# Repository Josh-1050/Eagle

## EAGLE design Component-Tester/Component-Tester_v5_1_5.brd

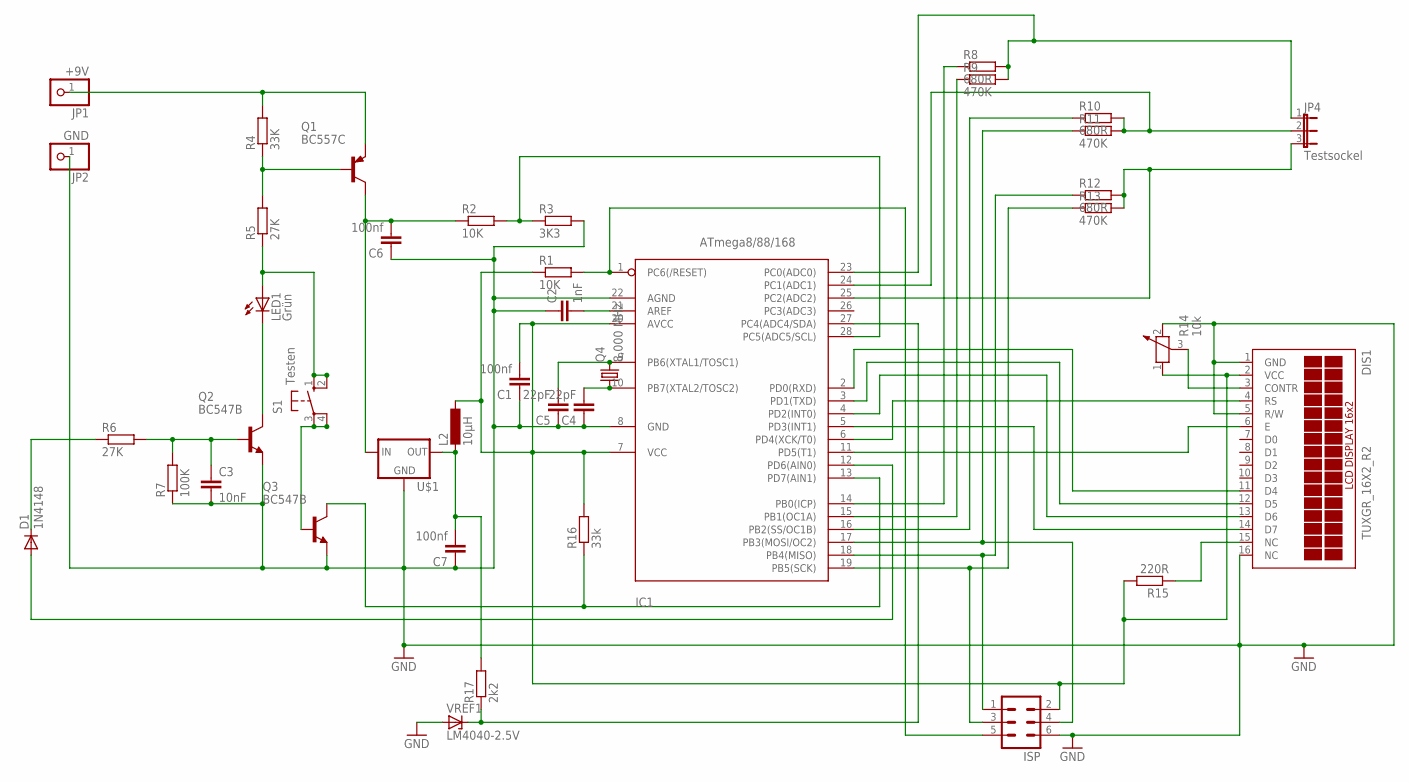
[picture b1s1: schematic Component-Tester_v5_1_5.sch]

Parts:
C1, C6, C7: 100nf; C5B3.5
C2: 1nF; C2.5-2
C3: 10nF; C5B3.5
C4, C5: 22pF; C025-025X050
D1: 1N4148; DO35-7
DIS1: TUXGR_16X2_R2
IC1: ATmega8/88/168; DIL28-3
ISP: ML6L
JP1: +9V; 1X01
JP2: GND; 1X01
JP4: Testsockel; JP2
L2: 10µH; 0207/10
LED1: Grün; LED5MM
Q1: BC557C; TO92-EBC
Q2, Q3: BC547B; TO92
Q4: 8,000 MHz; HC49/S
R1, R2: 10K; 0207/10
R3: 3K3; 0207/10
R4: 33K; 0207/10
R5, R6: 27K; 0207/10
R7: 100K; 0207/10
R8, R10, R12: 680R; 0207/10
R9, R11, R13: 470K; 0207/10
R14: 10k; PT-10
R15: 220R; 0207/10
R16: 33k; 0207/10
R17: 2k2; 0207/10
S1: Testen; B3F-10XX
U$1: MCP1702-5002; TO92-LOWDROP
VREF1: LM4040-2.5V; TO92-VREF

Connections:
GND: C1.1, C2.1, C3.2, C4.1, C5.1, C6.1, C7.1, DIS1.1 (GND), DIS1.5 (R/W), DIS1.16 (NC), IC1.8 (GND), IC1.22 (AGND), ISP.6, JP2.1, Q2.1 (E), Q3.1 (E), R3.2, R7.1, R14.2, U$1.GND, VREF1.-
unnamed: C6.2, Q1.C, R2.1, U$1.IN
unnamed: IC1.1 (PC6(/RESET)), ISP.5, R1.2
unnamed: C2.2, IC1.21 (AREF)
unnamed: Q1.B, R4.1, R5.2
unnamed: IC1.28 (PC5(ADC5/SCL)), R2.2, R3.1
unnamed: C1.2, DIS1.2 (VCC), IC1.7 (VCC), IC1.20 (AVCC), ISP.2, L2.1, R1.1, R14.1, R15.2, R16.2
unnamed: LED1.K (C), Q2.3 (C)
unnamed: IC1.13 (PD7(AIN1)), Q3.3 (C), R16.1
unnamed: C3.1, Q2.2 (B), R6.2, R7.2
unnamed: D1.A, IC1.12 (PD6(AIN0))
unnamed: IC1.25 (PC2(ADC2)), JP4.3, R12.2, R13.2
unnamed: Q3.2 (B), S1.3, S1.4 (P1)
unnamed: IC1.24 (PC1(ADC1)), JP4.2, R10.2, R11.2
unnamed: IC1.23 (PC0(ADC0)), JP4.1, R8.2, R9.2
unnamed: C7.2, L2.2, R17.2, U$1.OUT
unnamed: IC1.18 (PB4(MISO)), ISP.1, R12.1
unnamed: IC1.14 (PB0(ICP)), R8.1
unnamed: IC1.15 (PB1(OC1A)), R9.1
unnamed: IC1.16 (PB2(SS/OC1B)), R10.1
unnamed: IC1.19 (PB5(SCK)), ISP.3, R13.1
unnamed: LED1.A, R5.1, S1.1 (S), S1.2 (S1)
unnamed: DIS1.3 (CONTR), R14.3
unnamed: DIS1.4 (RS), IC1.6 (PD4(XCK/T0))
unnamed: DIS1.6 (E), IC1.11 (PD5(T1))
unnamed: DIS1.11 (D4), IC1.2 (PD0(RXD))
unnamed: DIS1.12 (D5), IC1.3 (PD1(TXD))
unnamed: DIS1.13 (D6), IC1.4 (PD2(INT0))
unnamed: DIS1.14 (D7), IC1.5 (PD3(INT1))
unnamed: C4.2, IC1.10 (PB7(XTAL2/TOSC2)), Q4.1
unnamed: DIS1.15 (NC), R15.1
unnamed: JP1.1, Q1.E, R4.2
unnamed: C5.2, IC1.9 (PB6(XTAL1/TOSC1)), Q4.2
unnamed: D1.C, R6.1
unnamed: IC1.17 (PB3(MOSI/OC2)), ISP.4, R11.1
unnamed: IC1.27 (PC4(ADC4/SDA)), R17.1, VREF1.+

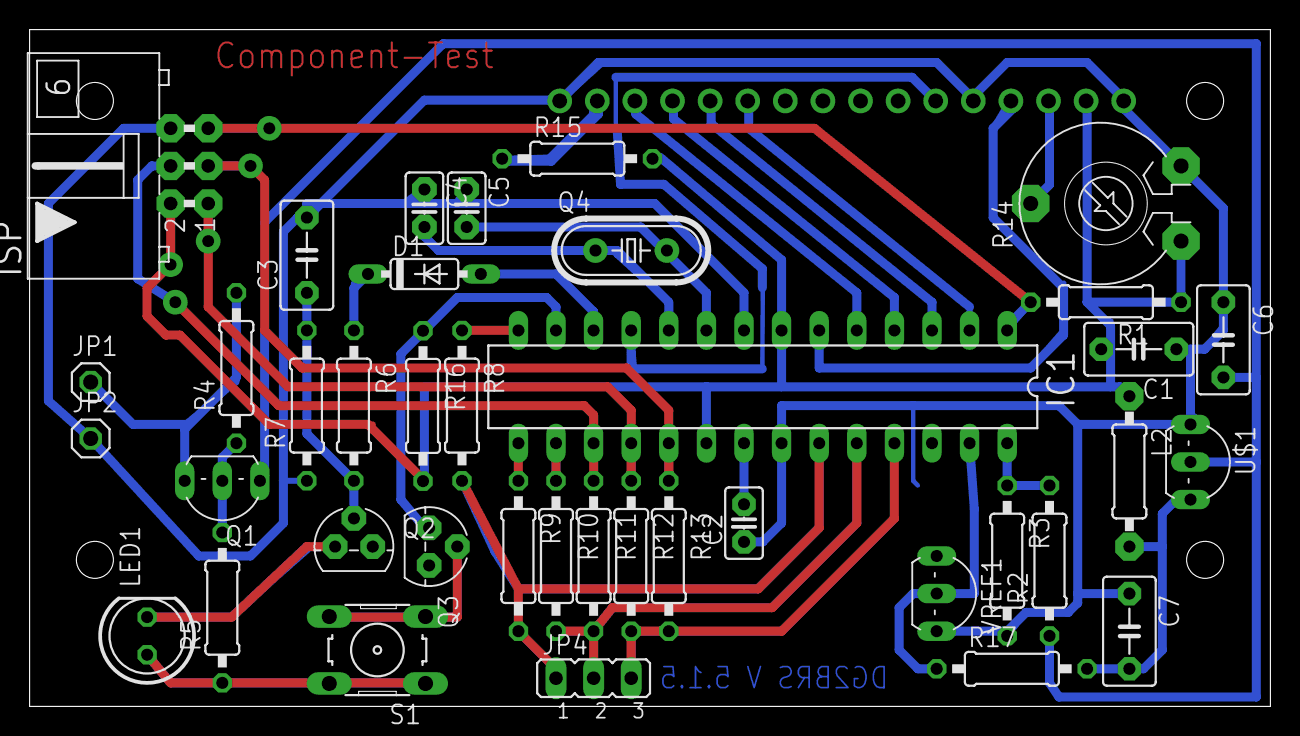
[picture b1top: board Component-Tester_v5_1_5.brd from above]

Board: 2 copper layers, 83.8 x 45.7 mm, 40 parts (1 on the bottom side), 36 nets.

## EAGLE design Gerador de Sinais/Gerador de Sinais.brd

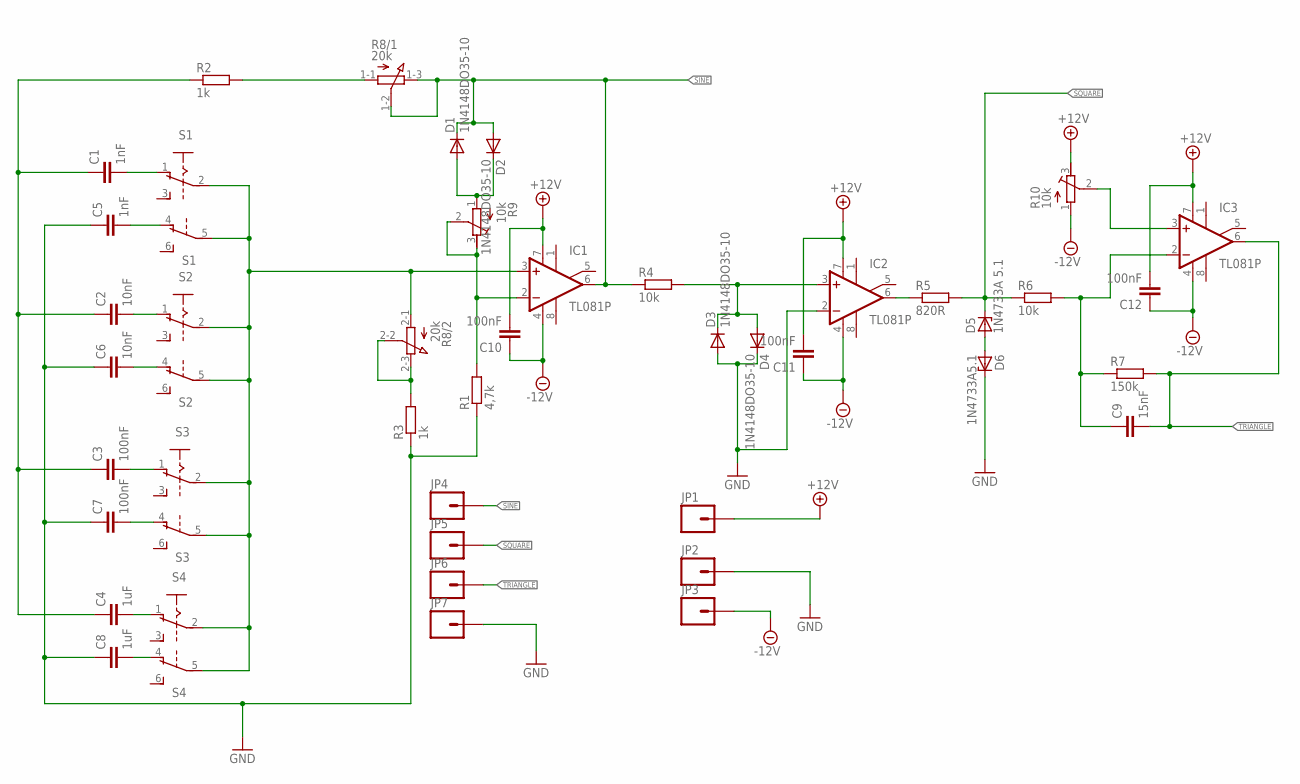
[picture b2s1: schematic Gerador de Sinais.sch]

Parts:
C1, C5: 1nF; C050-050X075
C2, C6: 10nF; C050-050X075
C3, C7, C10, C11, C12: 100nF; C050-050X075
C4, C8: 1uF; C050-050X075
C9: 15nF; C050-050X075
D1, D2, D3, D4: 1N4148DO35-10; DO35-10
D5: 1N4733A 5.1; ZDIO-10
D6: 1N4733A5.1; ZDIO-10
IC1, IC2, IC3: TL081P; DIL08
JP1, JP2, JP3, JP4, JP5, JP6, JP7: M01OFFSET; 1X01_OFFSET
R1: 4,7k; 0207/10
R2, R3: 1k; 0207/10
R4, R6: 10k; 0207/10
R5: 820R; 0207/10
R7: 150k; 0207/10
R8: 20k; 3RP/1610G
R9, R10: 10k; RTRIM3296X
S1, S2, S3, S4: A68-A31

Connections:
+12V: C10.2, C11.2, C12.2, IC1.7 (V+), IC2.7 (V+), IC3.7 (V+), JP1.1, R10.3 (E)
-12V: C10.1, C11.1, C12.1, IC1.4 (V-), IC2.4 (V-), IC3.4 (V-), JP3.1, R10.1 (A)
GND: C5.1, C6.1, C7.1, C8.1, D3.A, D4.C, D6.C, IC2.2 (-IN), JP2.1, JP7.1, R1.1, R3.1
unnamed: IC1.2 (-IN), R1.2, R9.2 (S), R9.3 (E)
unnamed: D5.A, D6.A
unnamed: R3.2, R8.2-2 (S), R8.2-3 (E)
unnamed: R2.2, R8.1-1 (A)
unnamed: IC1.3 (+IN), R8.2-1 (A), S1.2, S1.5, S2.2, S2.5, S3.2, S3.5, S4.2, S4.5
unnamed: D1.A, D2.C, R9.1 (A)
unnamed: C1.2, S1.1 (O)
unnamed: C5.2, S1.4 (O)
unnamed: C2.2, S2.1 (O)
unnamed: C6.2, S2.4 (O)
unnamed: C3.2, S3.1 (O)
unnamed: C4.2, S4.1 (O)
unnamed: C7.2, S3.4 (O)
unnamed: C8.2, S4.4 (O)
unnamed: C1.1, C2.1, C3.1, C4.1, R2.1
unnamed: IC2.6 (OUT), R5.1
unnamed: D3.C, D4.A, IC2.3 (+IN), R4.2
unnamed: C9.1, IC3.2 (-IN), R6.2, R7.1
unnamed: IC3.3 (+IN), R10.2 (S)
SINE: D1.C, D2.A, IC1.6 (OUT), JP4.1, R4.1, R8.1-2 (S), R8.1-3 (E)
SQUARE: D5.C, JP5.1, R5.2, R6.1
TRIANGLE: C9.2, IC3.6 (OUT), JP6.1, R7.2

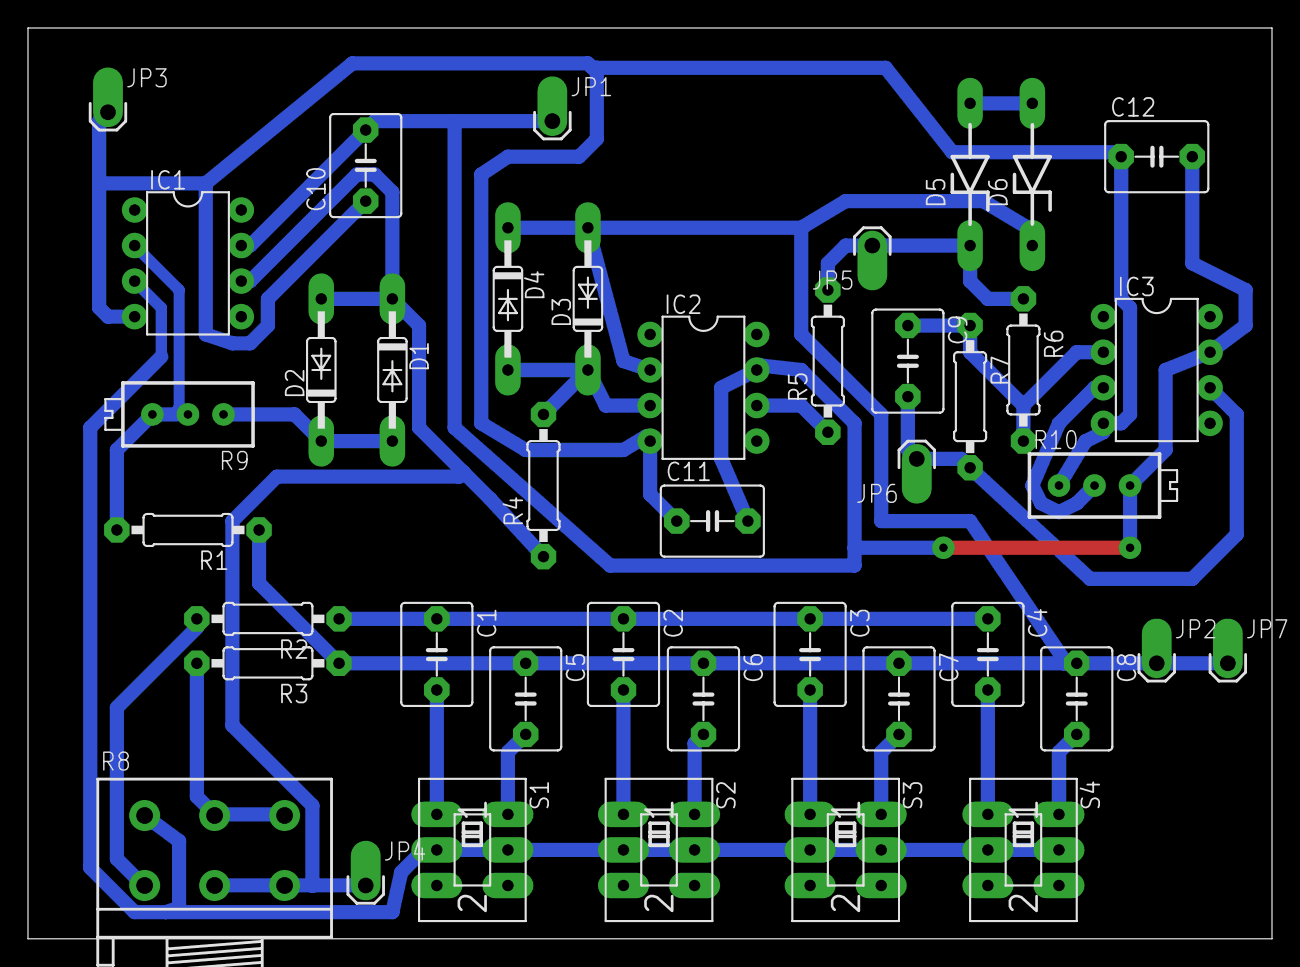
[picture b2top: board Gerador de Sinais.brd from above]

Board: 2 copper layers, 88.9 x 65.1 mm, 42 parts (0 on the bottom side), 25 nets.

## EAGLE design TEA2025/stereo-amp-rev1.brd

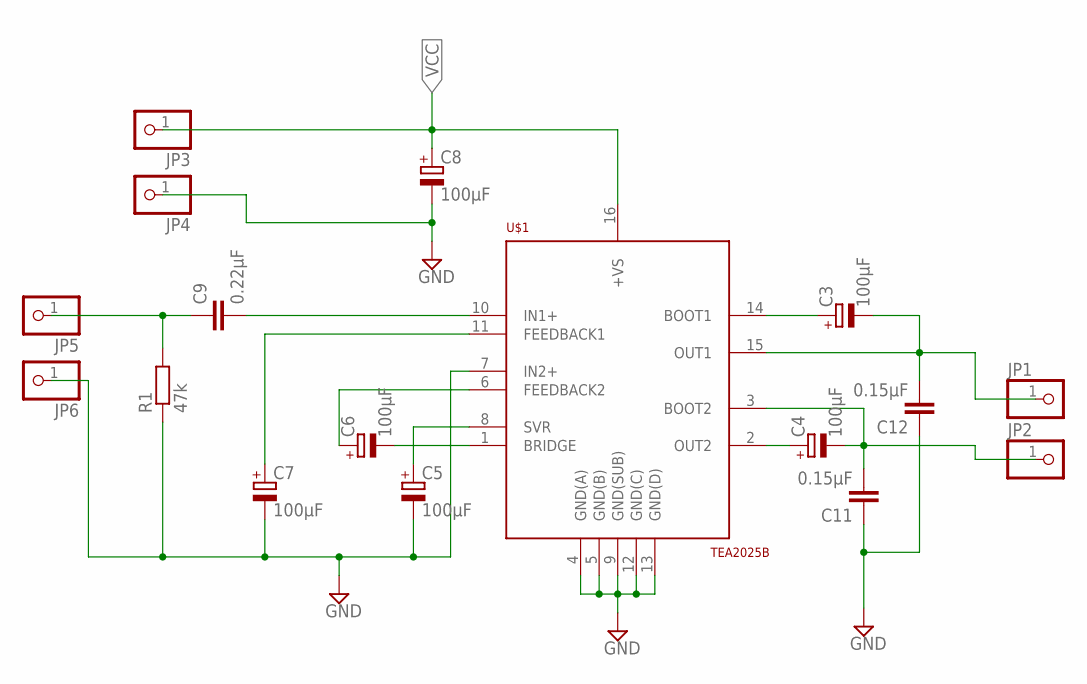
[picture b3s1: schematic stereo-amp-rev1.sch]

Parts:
C3, C4, C5, C6, C7, C8: 100µF; E2,5-7
C9: 0.22µF; C050-024X044
C11, C12: 0.15µF; C050-024X044
JP1, JP2, JP3, JP4, JP5, JP6: PINHD-1X1; 1X01
R1: 47k; 0207/10
U$1: TEA2025B; DIL16

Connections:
GND: C5.-, C7.-, C8.-, C11.1, C12.1, JP4.1, JP6.1, R1.1, U$1.4 (GND(A)), U$1.5 (GND(B)), U$1.7 (IN2+), U$1.9 (GND(SUB)), U$1.12 (GND(C)), U$1.13 (GND(D))
unnamed: C9.2, U$1.10 (IN1+)
unnamed: C6.-, U$1.1 (BRIDGE)
unnamed: C7.+, U$1.11 (FEEDBACK1)
unnamed: C6.+, U$1.6 (FEEDBACK2)
unnamed: C5.+, U$1.8 (SVR)
unnamed: C4.+, U$1.2 (OUT2)
unnamed: C4.-, C11.2, JP2.1, U$1.3 (BOOT2)
unnamed: C3.+, U$1.14 (BOOT1)
unnamed: C3.-, C12.2, JP1.1, U$1.15 (OUT1)
unnamed: C9.1, JP5.1, R1.2
VCC: C8.+, JP3.1, U$1.16 (+VS)

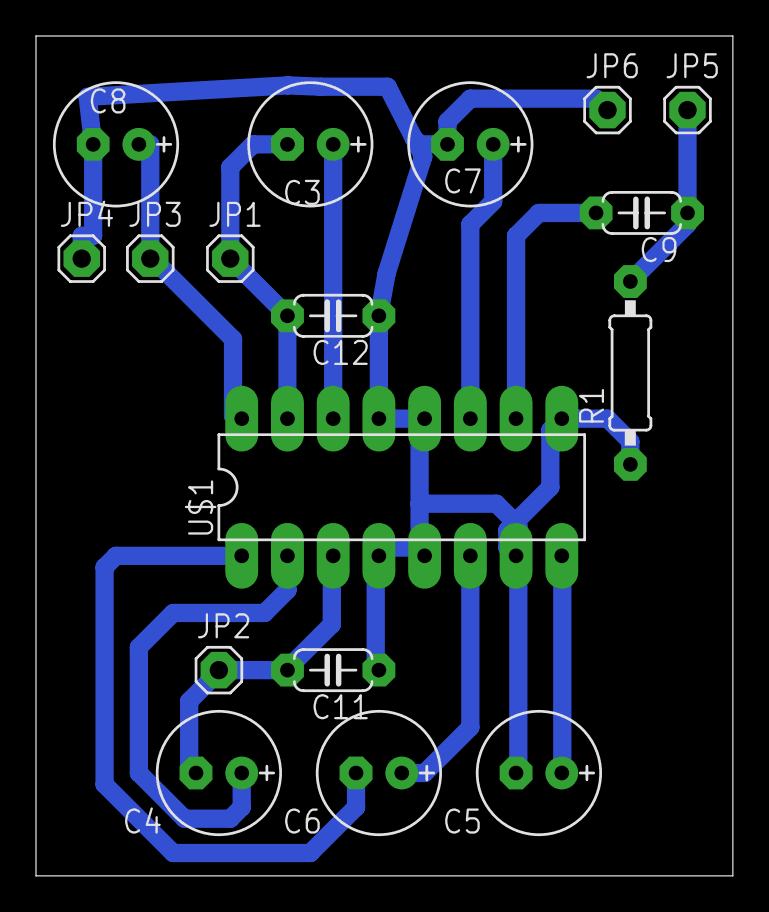
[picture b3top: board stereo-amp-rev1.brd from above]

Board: 2 copper layers, 38.7 x 46.7 mm, 17 parts (0 on the bottom side), 12 nets.

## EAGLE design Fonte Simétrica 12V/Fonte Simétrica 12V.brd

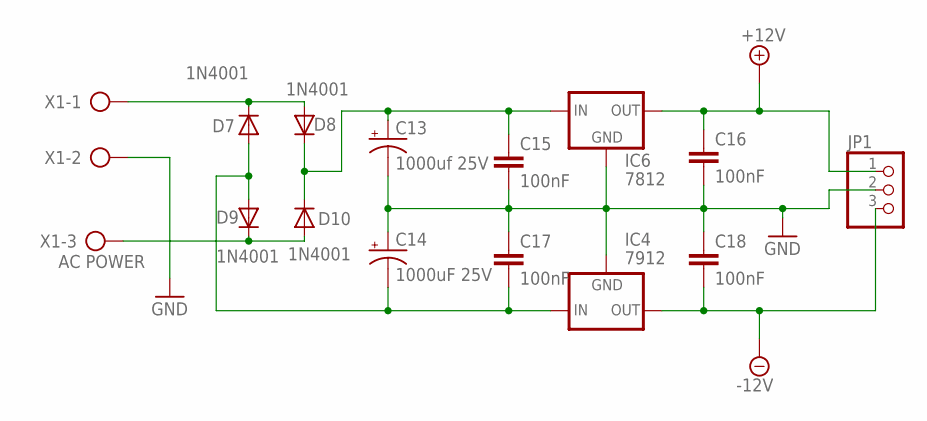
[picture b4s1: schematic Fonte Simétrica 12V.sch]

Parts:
C13: 1000uf 25V; E5-10,5
C14: 1000uF 25V; E5-10,5
C15, C16, C17, C18: 100nF; C025-040X050
D7, D8, D9, D10: 1N4001; DO41-10
IC4: 7912; 79XXS
IC6: 7812; 78XXS
JP1: PINHD-1X3; 1X03
X1: AC POWER; AK500/3

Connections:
+12V: C16.1, IC6.OUT, JP1.1
-12V: C18.2, IC4.OUT, JP1.3
GND: C13.-, C14.+, C15.2, C16.2, C17.1, C18.1, IC4.GND, IC6.GND, JP1.2, X1.2
unnamed: C14.-, C17.2, D7.A, D9.A, IC4.IN
unnamed: C13.+, C15.1, D8.C, D10.C, IC6.IN
unnamed: D7.C, D8.A, X1.1
unnamed: D9.C, D10.A, X1.3

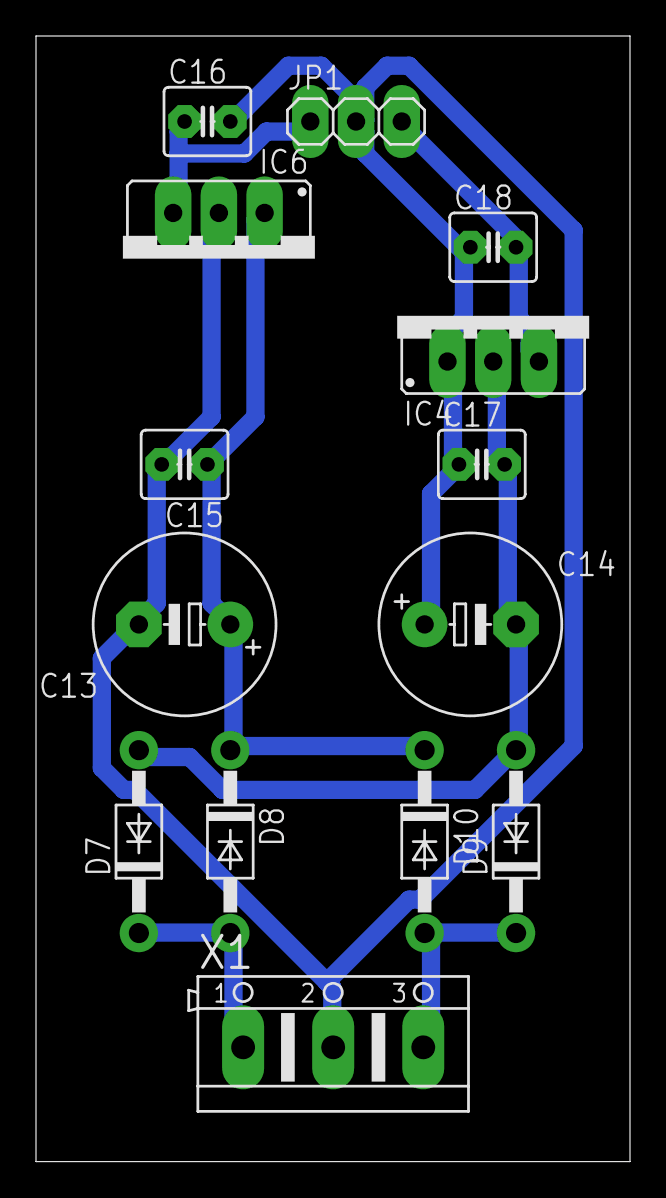
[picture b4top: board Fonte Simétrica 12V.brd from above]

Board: 2 copper layers, 33.0 x 62.5 mm, 14 parts (0 on the bottom side), 7 nets.

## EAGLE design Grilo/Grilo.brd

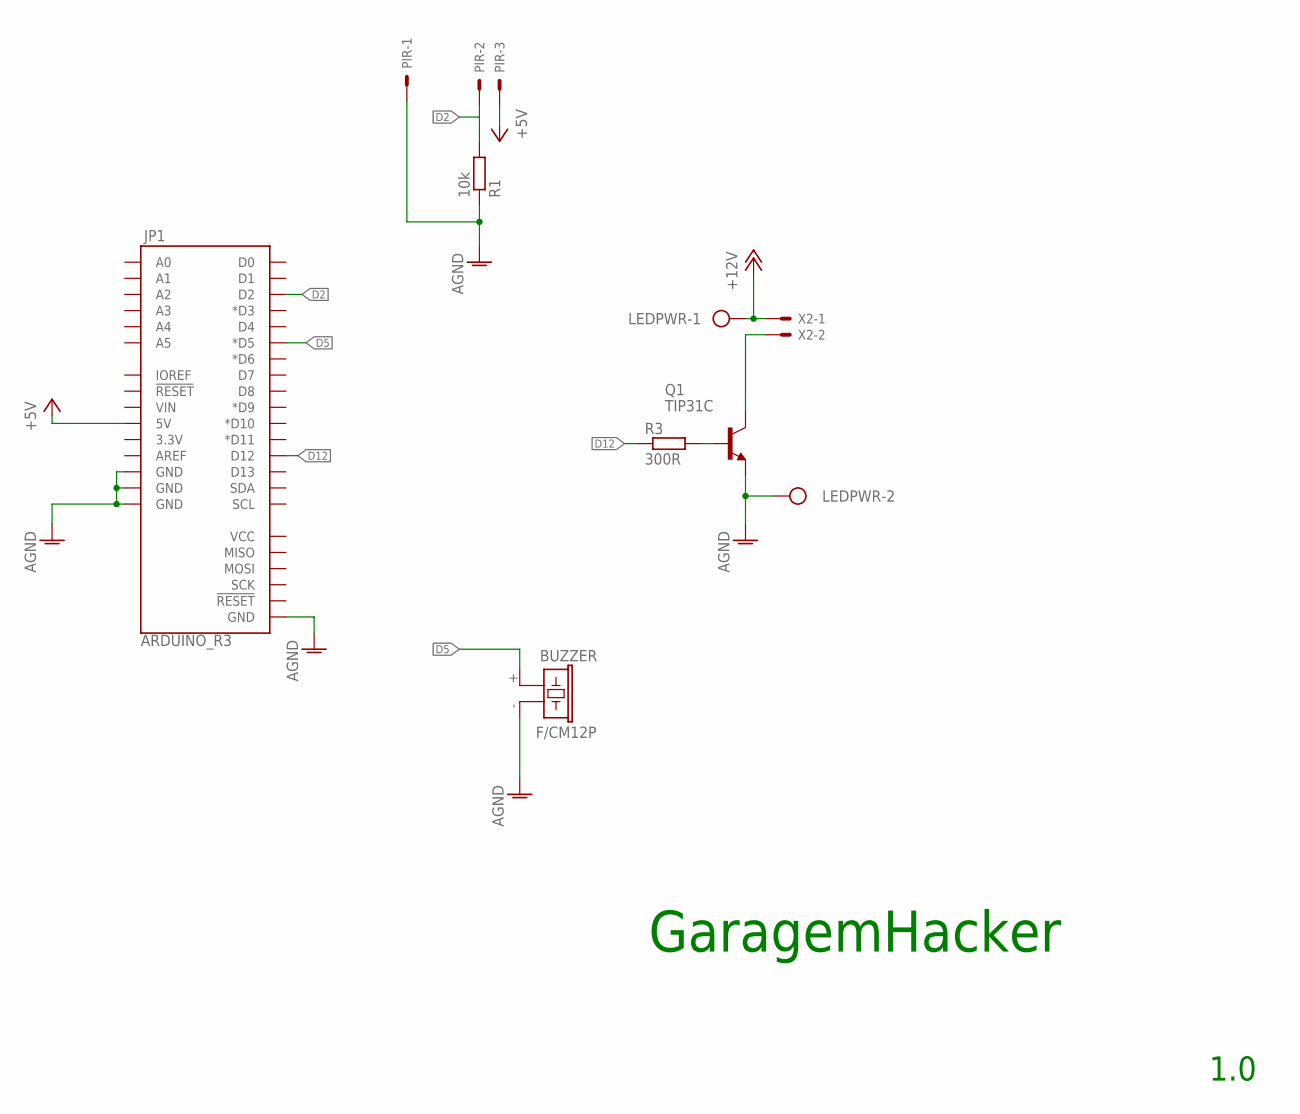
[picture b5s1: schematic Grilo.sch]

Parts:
BUZZER: F/CM12P
JP1: ARDUINO_R3
LEDPWR: AK500/2
PIR: KK-156-3
Q1: TIP31C; TO220V
R1: 10k; 0207/10
R3: 300R; 0207/10
X2: KK-156-2

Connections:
+5V: JP1.5V, PIR.3
+12V: LEDPWR.1, X2.1
AGND: BUZZER.- (2), JP1.GND@1 (GND), JP1.GND@2 (GND), JP1.GND@3 (GND), JP1.GND@4 (GND), LEDPWR.2, PIR.1, Q1.3 (E), R1.1
D2: JP1.D2, PIR.2, R1.2
D5: BUZZER.+ (1), JP1.D5 (*D5)
D12: JP1.D12, R3.1
unnamed: Q1.1 (B), R3.2
unnamed: Q1.2 (C), X2.2

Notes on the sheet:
1.0
GaragemHacker

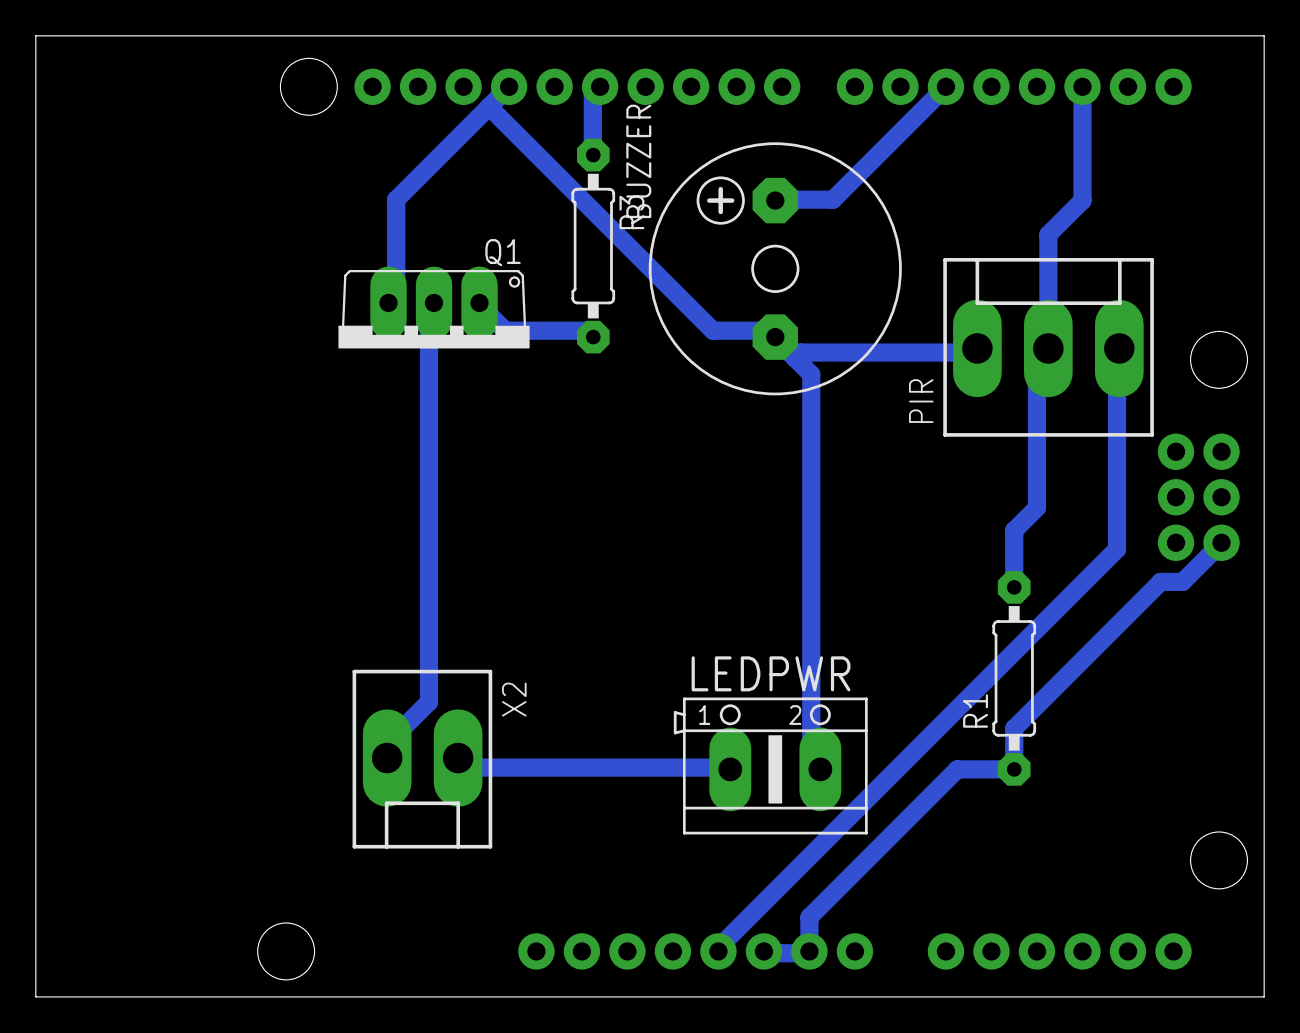
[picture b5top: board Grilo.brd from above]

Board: 2 copper layers, 68.6 x 53.6 mm, 8 parts (0 on the bottom side), 8 nets.

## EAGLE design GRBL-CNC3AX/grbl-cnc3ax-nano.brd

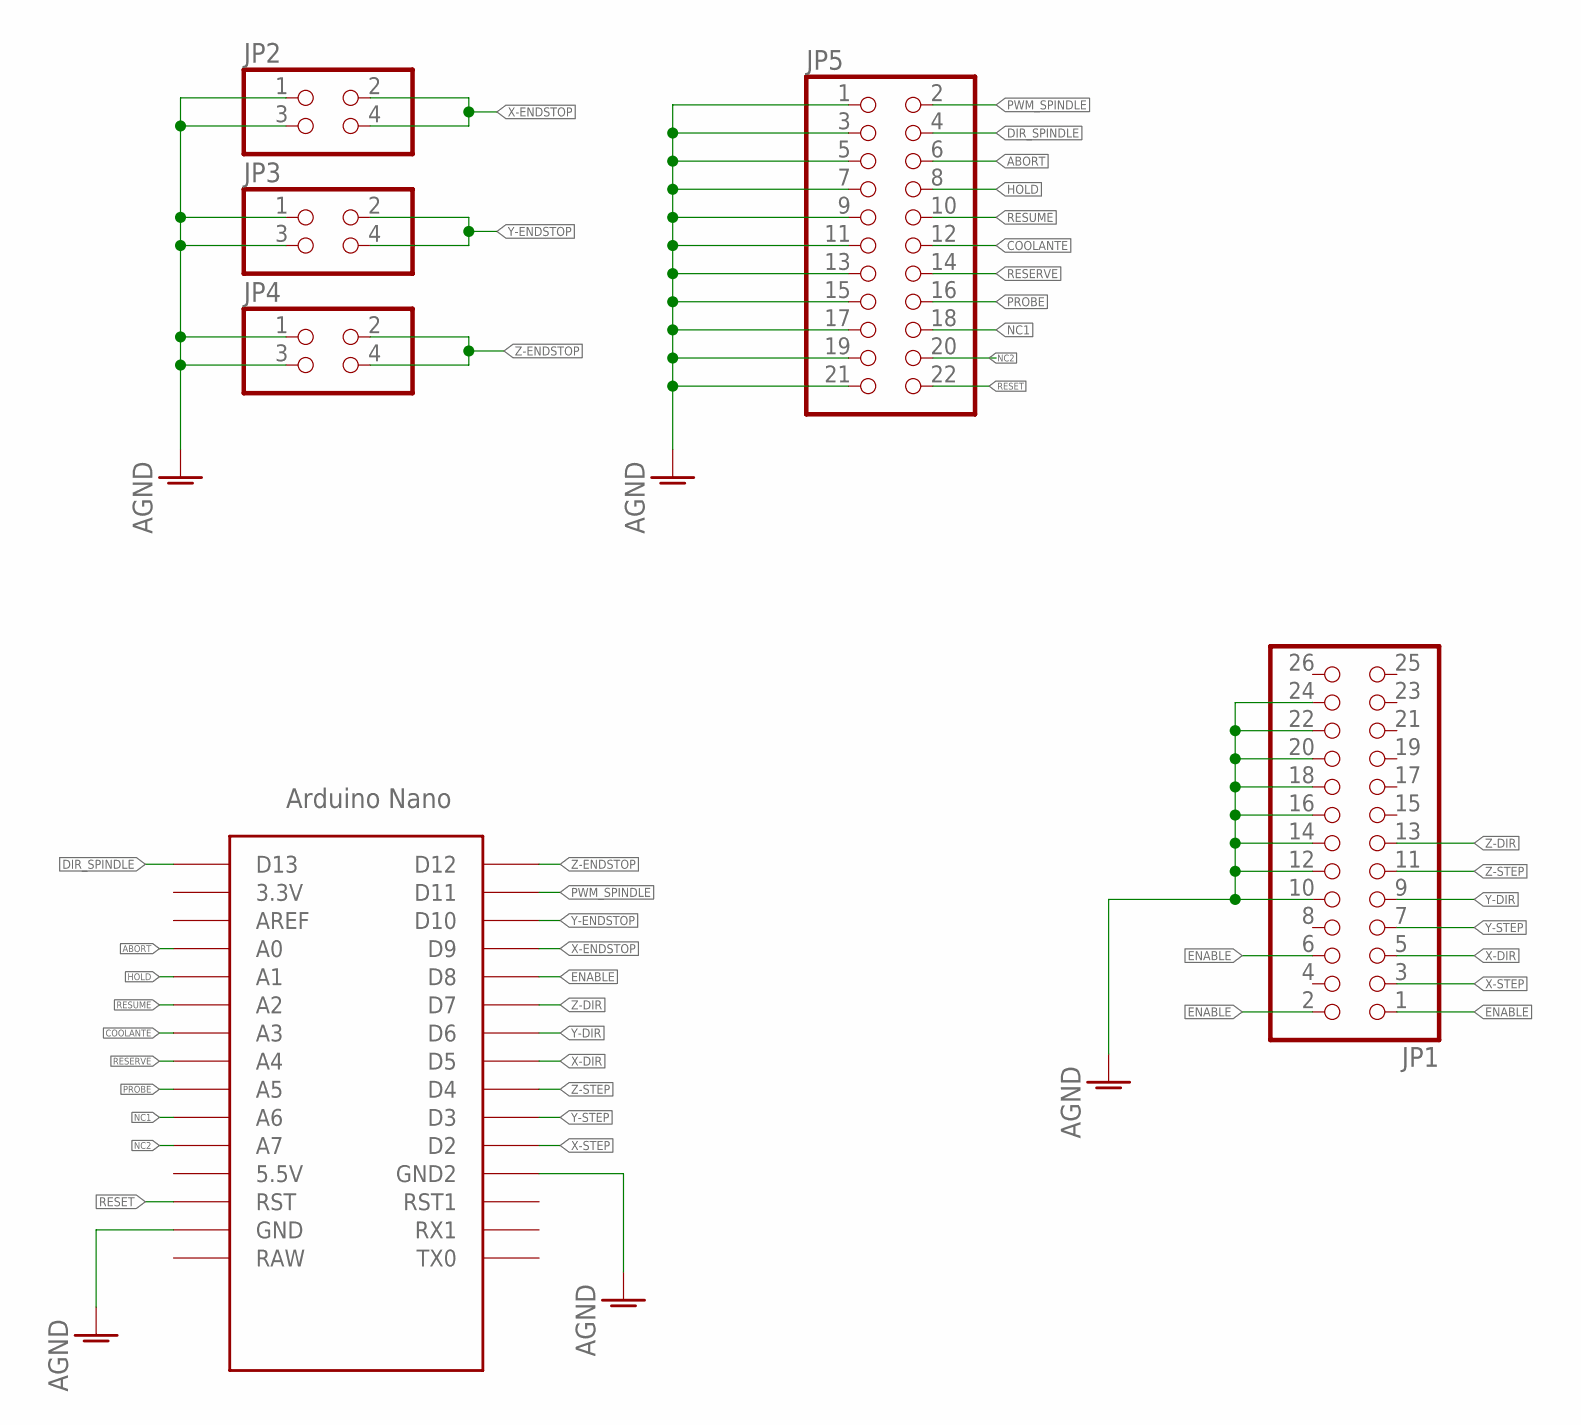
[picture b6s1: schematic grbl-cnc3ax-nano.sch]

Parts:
JP1: PINHD-2X13; 2X13
JP2, JP3, JP4: PINHD-2X2; 2X02
JP5: PINHD-2X11; 2X11
U$1: NANO

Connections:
ABORT: JP5.6, U$1.A0
AGND: JP1.10, JP1.12, JP1.14, JP1.16, JP1.18, JP1.20, JP1.22, JP1.24, JP2.1, JP2.3, JP3.1, JP3.3, JP4.1, JP4.3, JP5.1, JP5.3, JP5.5, JP5.7, JP5.9, JP5.11, JP5.13, JP5.15, JP5.17, JP5.19, JP5.21, U$1.GND, U$1.GND1 (GND2)
COOLANTE: JP5.12, U$1.A3
DIR_SPINDLE: JP5.4, U$1.D13
ENABLE: JP1.1, JP1.2, JP1.6, U$1.D8
HOLD: JP5.8, U$1.A1
NC1: JP5.18, U$1.A6
NC2: JP5.20, U$1.A7
PROBE: JP5.16, U$1.A5
PWM_SPINDLE: JP5.2, U$1.D11
RESERVE: JP5.14, U$1.A4
RESET: JP5.22, U$1.RST
RESUME: JP5.10, U$1.A2
X-DIR: JP1.5, U$1.D5
X-ENDSTOP: JP2.2, JP2.4, U$1.D9
X-STEP: JP1.3, U$1.D2
Y-DIR: JP1.9, U$1.D6
Y-ENDSTOP: JP3.2, JP3.4, U$1.D10
Y-STEP: JP1.7, U$1.D3
Z-DIR: JP1.13, U$1.D7
Z-ENDSTOP: JP4.2, JP4.4, U$1.D12
Z-STEP: JP1.11, U$1.D4

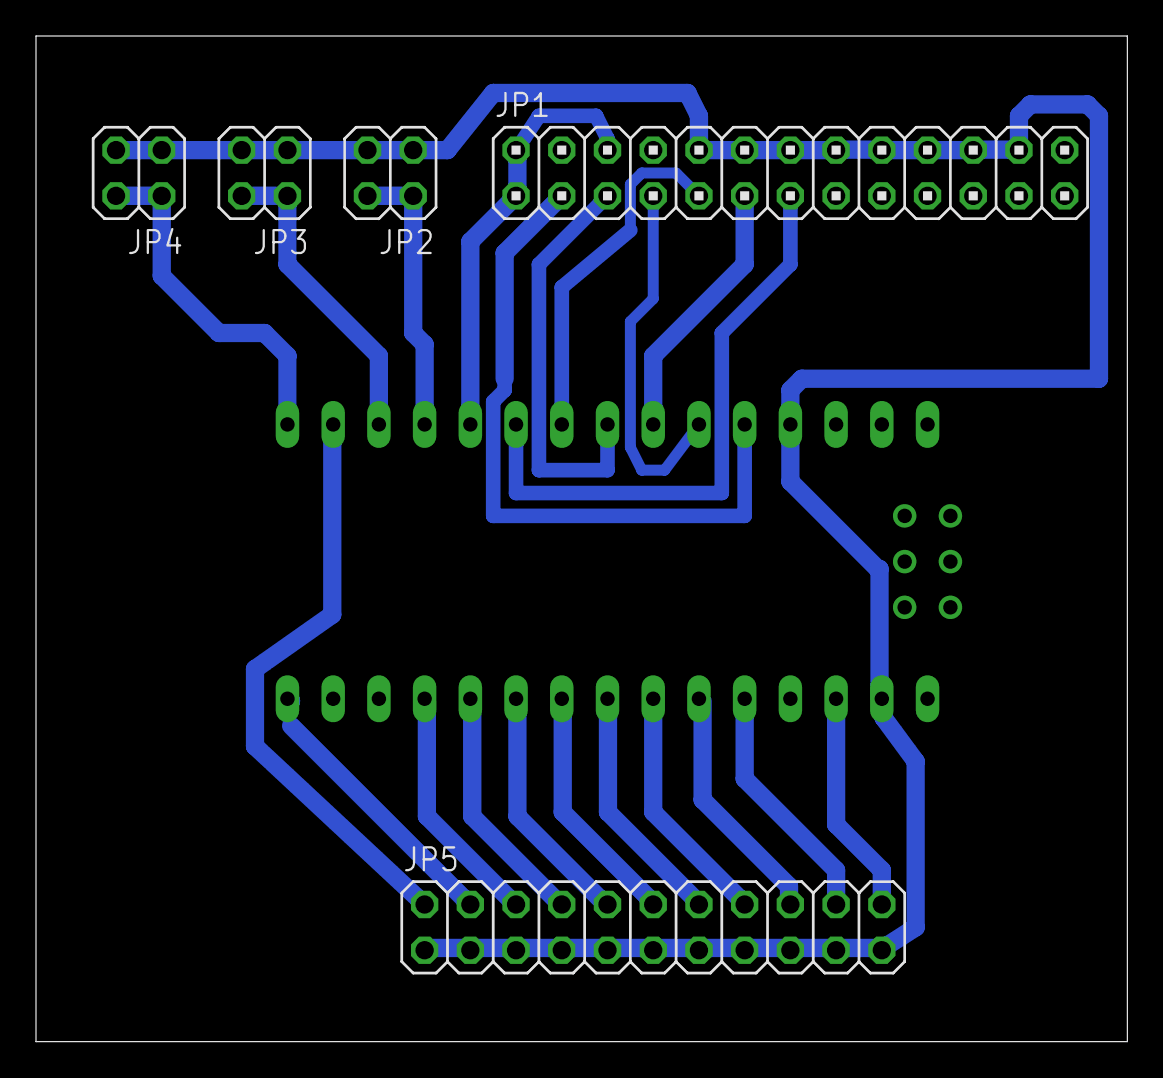
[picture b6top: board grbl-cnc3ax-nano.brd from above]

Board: 2 copper layers, 60.6 x 55.9 mm, 6 parts (0 on the bottom side), 22 nets.

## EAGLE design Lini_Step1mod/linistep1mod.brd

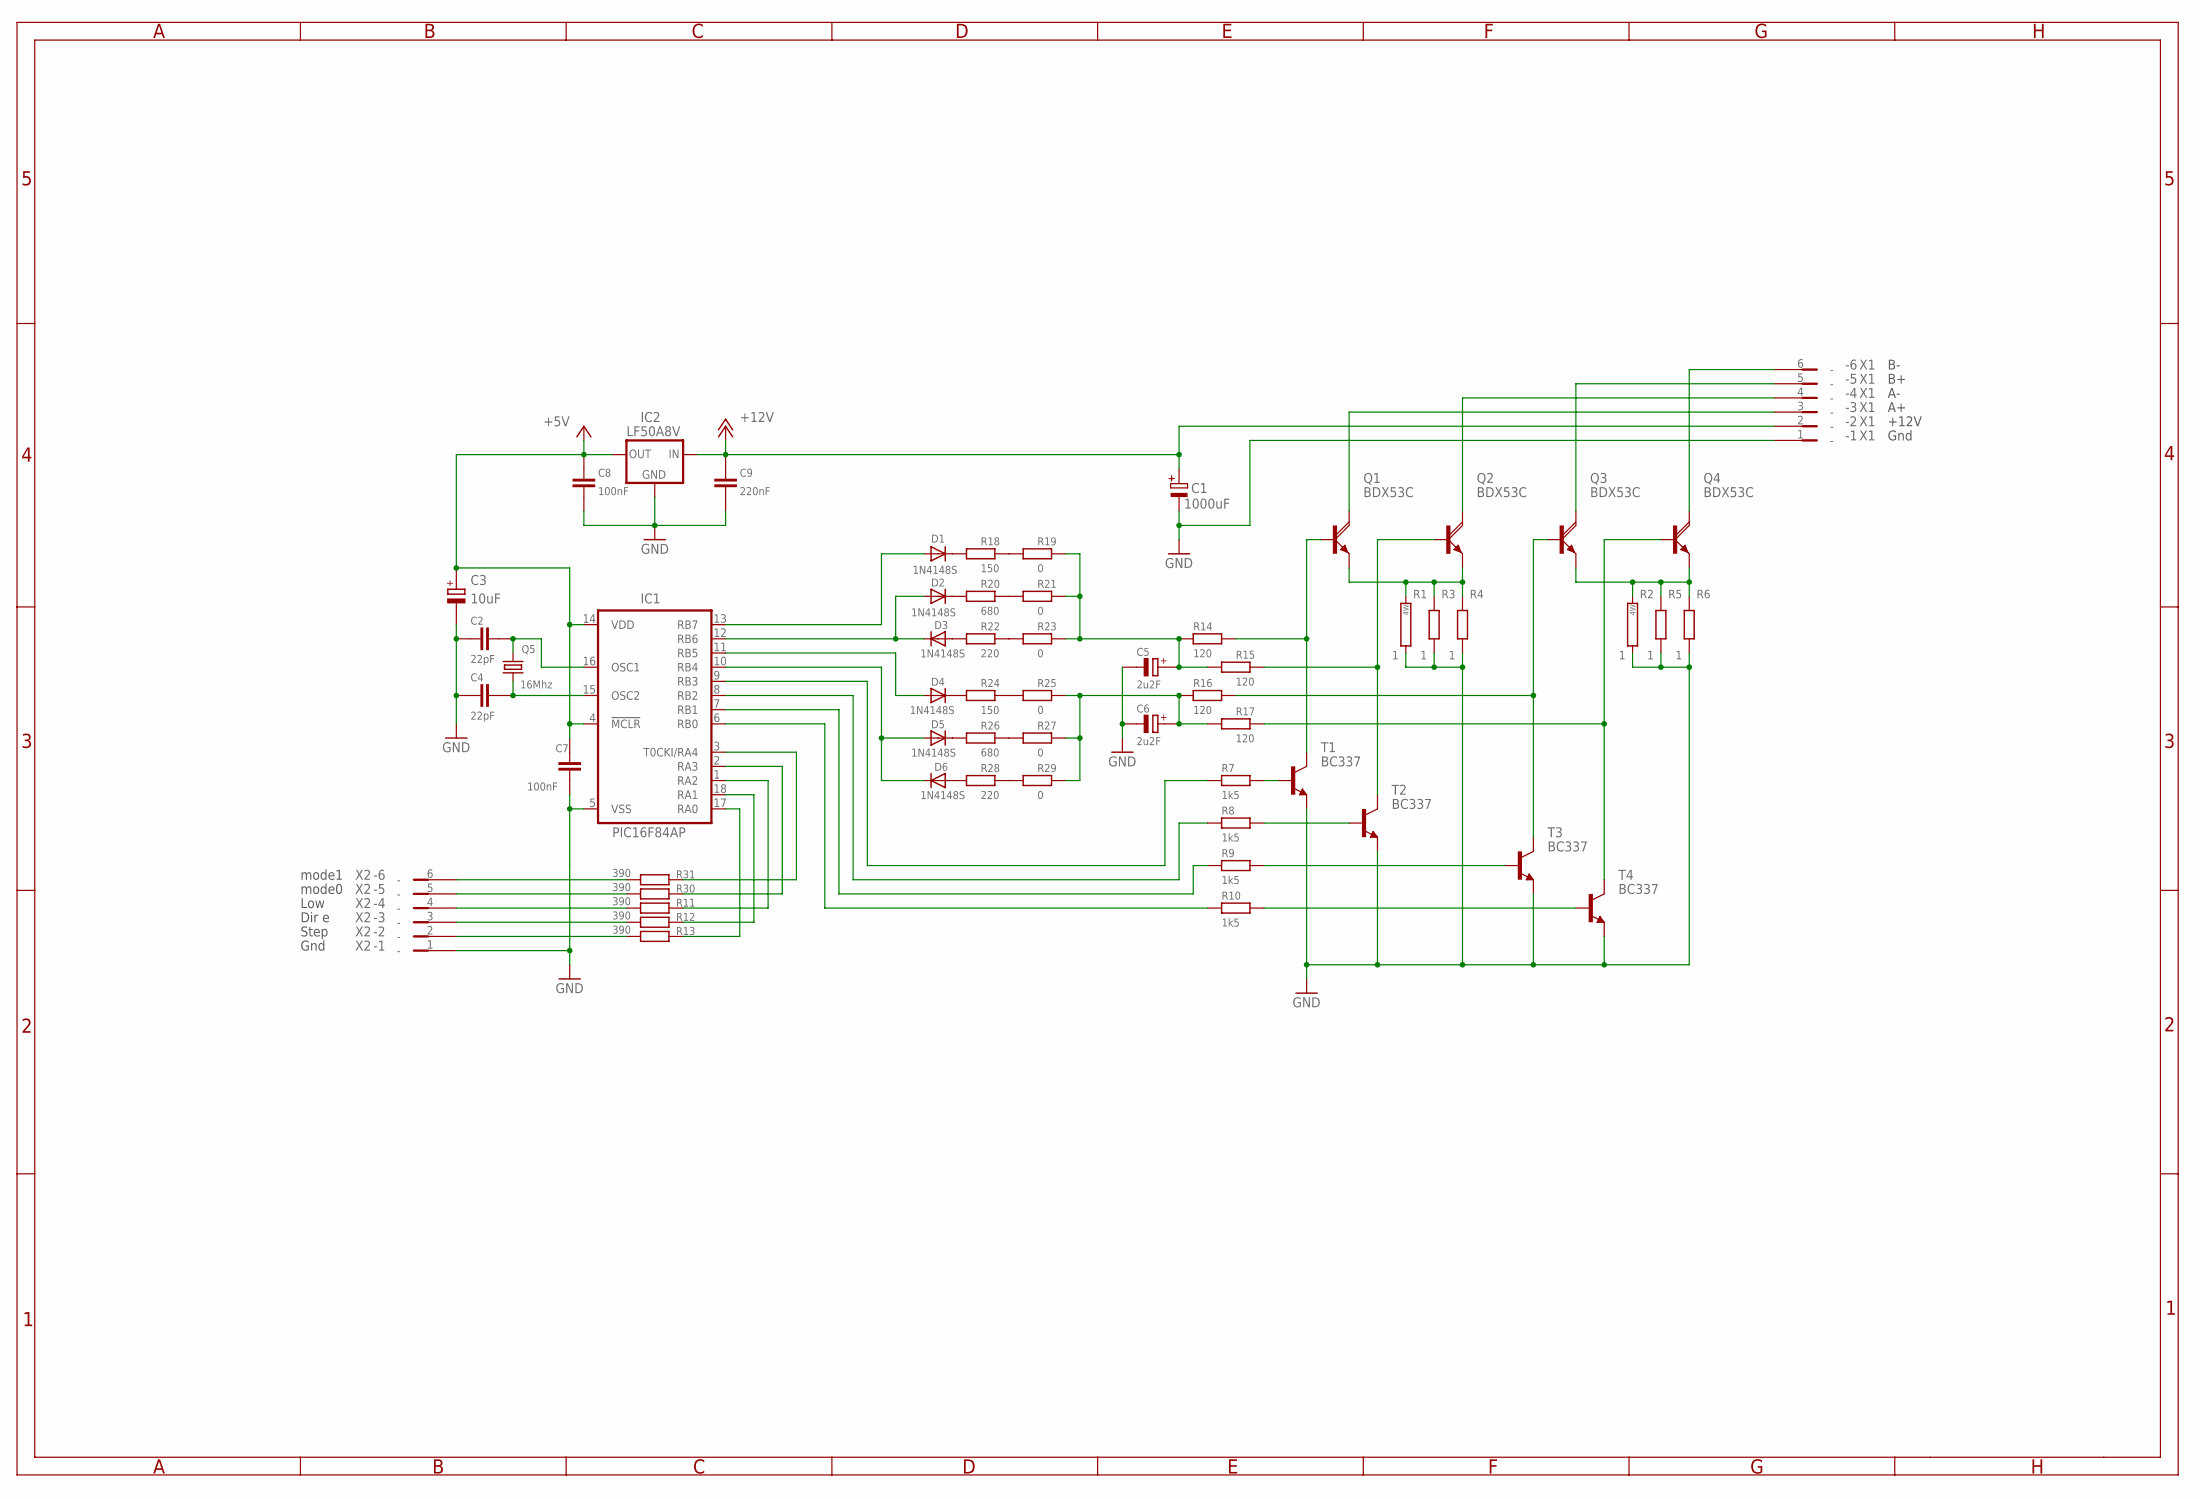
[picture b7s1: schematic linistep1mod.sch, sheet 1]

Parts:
C1: 1000uF; E5-10,5
C2, C4: 22pF; CAPC2012X145AN
C3: 10uF; CAPMP3528X210N
C5, C6: 2u2F; CAPMP3216X180N
C7, C8: 100nF; CAPC2012X145AN
C9: 220nF; CAPC3225X168N
D1, D2, D3, D4, D5, D6: 1N4148S; DO35-7A
IC1: PIC16F84AP; DIL18
IC2: LF50A8V; 78XXL
Q1, Q2, Q3, Q4: BDX53C; TO220AHS
Q5: 16Mhz; HC49/S
R1, R2: 1; 206A
R3, R4, R5, R6: 1; 0411/12
R7, R8, R9, R10: 1k5; RESC3115X70N
R11, R12, R13, R30, R31: 390; RESC3115X70N
R14, R15, R16, R17: 120; RESC3115X70N
R18, R24: 150; RESC3115X70N
R19, R21, R23, R25, R27, R29: 0; RESC3115X70N
R20, R26: 680; RESC3115X70N
R22, R28: 220; RESC3115X70N
T1, T2, T3, T4: BC337; TO92
X1, X2: RIACON-6

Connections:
+5V: C3.+, C7.2, C8.2, IC1.4 (!MCLR), IC1.14 (VDD), IC2.OUT
+12V: C1.+, C9.2, IC2.IN, X1.2
GND: C1.-, C2.1, C3.-, C4.1, C5.-, C6.-, C7.1, C8.1, C9.1, IC1.5 (VSS), IC2.GND, R1.1, R2.1, R3.1, R4.1, R5.1, R6.1, T1.1 (E), T2.1 (E), T3.1 (E), T4.1 (E), X1.1, X2.1
unnamed: Q1.E, Q2.E, R1.2, R3.2, R4.2
unnamed: D3.A, R22.1
unnamed: D2.C, R20.1
unnamed: R7.2, T1.2 (B)
unnamed: Q3.E, Q4.E, R2.2, R5.2, R6.2
unnamed: R8.2, T2.2 (B)
unnamed: R31.1, X2.6
unnamed: R9.2, T3.2 (B)
unnamed: Q4.B, R17.2, T4.3 (C)
unnamed: Q3.B, R16.2, T3.3 (C)
unnamed: Q2.B, R15.2, T2.3 (C)
unnamed: Q1.B, R14.2, T1.3 (C)
unnamed: R10.2, T4.2 (B)
unnamed: Q4.C, X1.6
unnamed: Q3.C, X1.5
unnamed: Q2.C, X1.4
unnamed: Q1.C, X1.3
unnamed: D1.C, R18.1
unnamed: D4.C, R24.1
unnamed: R30.1, X2.5
unnamed: R18.2, R19.1
unnamed: R20.2, R21.1
unnamed: R22.2, R23.1
unnamed: R24.2, R25.1
unnamed: D5.C, R26.1
unnamed: D6.A, R28.1
unnamed: C6.+, R16.1, R17.1, R25.2, R27.2, R29.2
unnamed: C5.+, R14.1, R15.1, R19.2, R21.2, R23.2
unnamed: R26.2, R27.1
unnamed: R28.2, R29.1
unnamed: R11.1, X2.4
unnamed: D5.A, D6.C, IC1.10 (RB4)
unnamed: C2.2, IC1.16 (OSC1), Q5.2
unnamed: R12.1, X2.3
unnamed: R13.1, X2.2
unnamed: IC1.6 (RB0), R10.1
unnamed: IC1.7 (RB1), R9.1
unnamed: IC1.8 (RB2), R8.1
unnamed: IC1.9 (RB3), R7.1
unnamed: D4.A, IC1.11 (RB5)
unnamed: C4.2, IC1.15 (OSC2), Q5.1
unnamed: D1.A, IC1.13 (RB7)
unnamed: IC1.3 (T0CKI/RA4), R31.2
unnamed: IC1.2 (RA3), R30.2
unnamed: IC1.1 (RA2), R11.2
unnamed: IC1.18 (RA1), R12.2
unnamed: IC1.17 (RA0), R13.2
unnamed: D2.A, D3.C, IC1.12 (RB6)

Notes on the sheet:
Gnd
mode1
mode0
Low
Step
Dir e
+12V

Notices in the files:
parts and their libraries:
SparkFun-Connectors: Licensing: Creative Commons ShareAlike 4.0 International - https://creativecommons.org/licenses/by-sa/4.0
